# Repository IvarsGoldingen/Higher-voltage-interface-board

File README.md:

# Higher voltage interface board

The device can be used to interface higher voltage DC systems. This specific device is intended for 24VDC.

## Features

* 4 high side transistor outputs;
* 6 inputs using voltage dividers;
* 4 relay outputs;
* 2 buttons;
* 1 LED;
* EEPROM via SPI;
* 2 seperate 5V power inputs: one for relays, the other for other components. Can be jumped together.

## Photos

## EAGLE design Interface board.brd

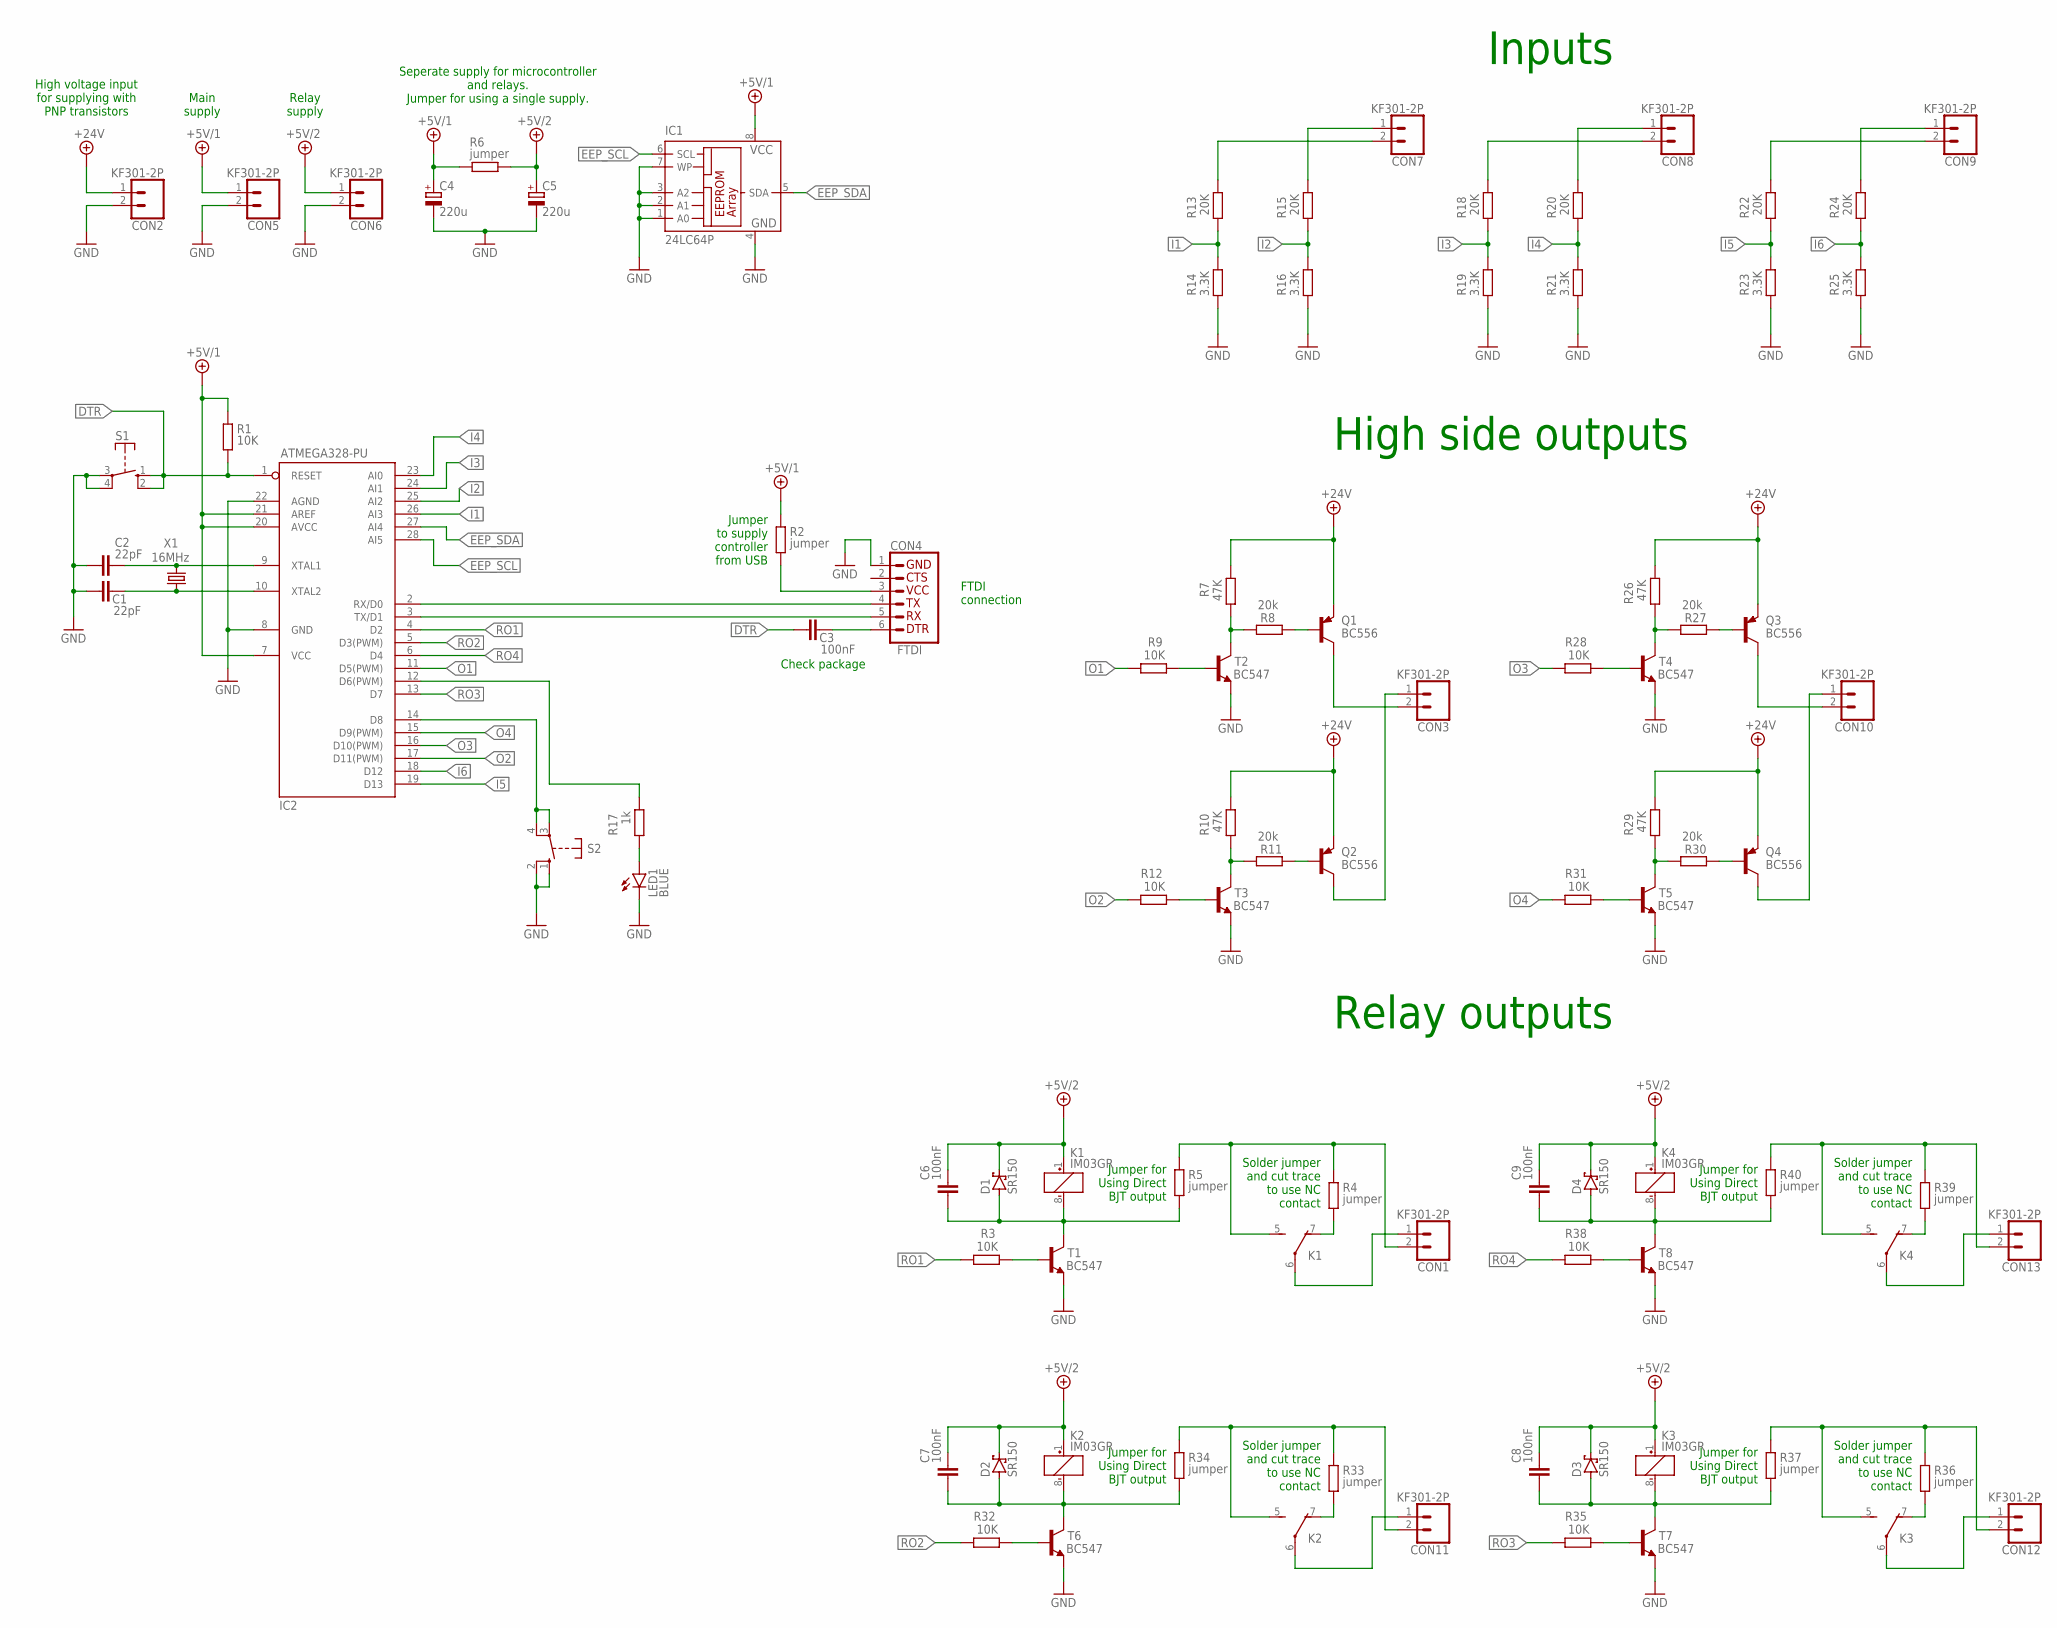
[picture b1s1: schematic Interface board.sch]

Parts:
C1, C2: 22pF; C050-024X044
C3, C6, C7, C8, C9: 100nF; C050-024X044
C4, C5: 220u; E5-10,5
CON1, CON2, CON3, CON5, CON6, CON7, CON8, CON9, CON10, CON11, CON12, CON13: KF301-2P
CON4: FTDI; 1X06_W_REC_GND
D1, D2, D3, D4: SR150; DO41-7.6
IC1: 24LC64P; DIL8
IC2: ATMEGA328-PU; DIL28-3
K1, K2, K3, K4: IM03GR
LED1: BLUE; LED5MM
Q1, Q2, Q3, Q4: BC556; TO92-EBC
R1, R3, R9, R12, R28, R31, R32, R35, R38: 10K; 0204/7
R2, R4, R5, R6, R33, R34, R36, R37, R39, R40: jumper; R0805
R7, R10, R26, R29: 47K; 0204/7
R8, R11, R27, R30: 20k; 0204/7
R13, R15, R18, R20, R22, R24: 20K; 0204/7
R14, R16, R19, R21, R23, R25: 3.3K; 0204/7
R17: 1k; 0204/7
S1, S2: RACON12
T1, T2, T3, T4, T5, T6, T7, T8: BC547; TO92
X1: 16MHz; HC49

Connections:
+5V/1: C4.+, CON5.1, IC1.8 (VCC), IC2.7 (VCC), IC2.20 (AVCC), IC2.21 (AREF), R1.1, R2.1, R6.1
+5V/2: C5.+, C6.1, C7.1, C8.1, C9.1, CON6.1, D1.C, D2.C, D3.C, D4.C, K1.1 (+), K2.1 (+), K3.1 (+), K4.1 (+), R6.2
+24V: CON2.1, Q1.E, Q2.E, Q3.E, Q4.E, R7.2, R10.2, R26.2, R29.2
DTR: C3.2, IC2.1 (RESET), R1.2, S1.1 (S), S1.2 (S)
EEP_SCL: IC1.6 (SCL), IC2.28 (AI5)
EEP_SDA: IC1.5 (SDA), IC2.27 (AI4)
GND: C1.2, C2.2, C4.-, C5.-, CON2.2, CON4.1 (6), CON5.2, CON6.2, IC1.1 (A0), IC1.2 (A1), IC1.3 (A2), IC1.4 (GND), IC1.7 (WP), IC2.8 (GND), IC2.22 (AGND), LED1.K (C), R14.1, R16.1, R19.1, R21.1, R23.1, R25.1, S1.3, S1.4, S2.1 (S), S2.2 (S), T1.1 (E), T2.1 (E), T3.1 (E), T4.1 (E), T5.1 (E), T6.1 (E), T7.1 (E), T8.1 (E)
I1: IC2.26 (AI3), R13.1, R14.2
I2: IC2.25 (AI2), R15.1, R16.2
I3: IC2.24 (AI1), R18.1, R19.2
I4: IC2.23 (AI0), R20.1, R21.2
I5: IC2.19 (D13), R22.1, R23.2
I6: IC2.18 (D12), R24.1, R25.2
unnamed: C1.1, IC2.10 (XTAL2), X1.2
unnamed: C2.1, IC2.9 (XTAL1), X1.1
unnamed: IC2.12 (D6(PWM)), R17.2
unnamed: CON4.4 (3), IC2.2 (RX/D0)
unnamed: CON4.5 (2), IC2.3 (TX/D1)
unnamed: C3.1, CON4.6 (1)
unnamed: IC2.14 (D8), S2.3, S2.4
unnamed: CON4.3 (4), R2.2
unnamed: R3.2, T1.2 (B)
unnamed: R9.2, T2.2 (B)
unnamed: CON1.1, K1.6
unnamed: K1.7 (O), R4.2
unnamed: CON1.2, K1.5 (S), R4.1, R5.1
unnamed: R38.2, T8.2 (B)
unnamed: R7.1, R8.2, T2.3 (C)
unnamed: Q1.B, R8.1
unnamed: C6.2, D1.A, K1.8 (-), R5.2, T1.3 (C)
unnamed: R10.1, R11.2, T3.3 (C)
unnamed: Q2.B, R11.1
unnamed: R12.2, T3.2 (B)
unnamed: CON3.2, Q1.C
unnamed: CON3.1, Q2.C
unnamed: R32.2, T6.2 (B)
unnamed: CON11.1, K2.6
unnamed: CON13.1, K4.6
unnamed: CON7.2, R13.2
unnamed: CON13.2, K4.5 (S), R39.1, R40.1
unnamed: CON7.1, R15.2
unnamed: LED1.A, R17.1
unnamed: CON9.2, R22.2
unnamed: CON8.2, R18.2
unnamed: CON9.1, R24.2
unnamed: CON8.1, R20.2
unnamed: R26.1, R27.2, T4.3 (C)
unnamed: Q3.B, R27.1
unnamed: K4.7 (O), R39.2
unnamed: CON11.2, K2.5 (S), R33.1, R34.1
unnamed: K2.7 (O), R33.2
unnamed: C9.2, D4.A, K4.8 (-), R40.2, T8.3 (C)
unnamed: C7.2, D2.A, K2.8 (-), R34.2, T6.3 (C)
unnamed: R28.2, T4.2 (B)
unnamed: R29.1, R30.2, T5.3 (C)
unnamed: Q4.B, R30.1
unnamed: R31.2, T5.2 (B)
unnamed: CON10.2, Q3.C
unnamed: CON10.1, Q4.C
unnamed: R35.2, T7.2 (B)
unnamed: CON12.1, K3.6
unnamed: CON12.2, K3.5 (S), R36.1, R37.1
unnamed: K3.7 (O), R36.2
unnamed: C8.2, D3.A, K3.8 (-), R37.2, T7.3 (C)
O1: IC2.11 (D5(PWM)), R9.1
O2: IC2.17 (D11(PWM)), R12.1
O3: IC2.16 (D10(PWM)), R28.1
O4: IC2.15 (D9(PWM)), R31.1
RO1: IC2.4 (D2), R3.1
RO2: IC2.5 (D3(PWM)), R32.1
RO3: IC2.13 (D7), R35.1
RO4: IC2.6 (D4), R38.1

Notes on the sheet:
FTDI connection
Check package
Jumper to supply controller from USB
Solder jumper and cut trace to use NC contact
Jumper for Using Direct BJT output
Seperate supply for microcontroller and relays. Jumper for using a single supply.
High voltage input for supplying with PNP transistors
Main supply
Relay supply
Inputs
High side outputs
Relay outputs

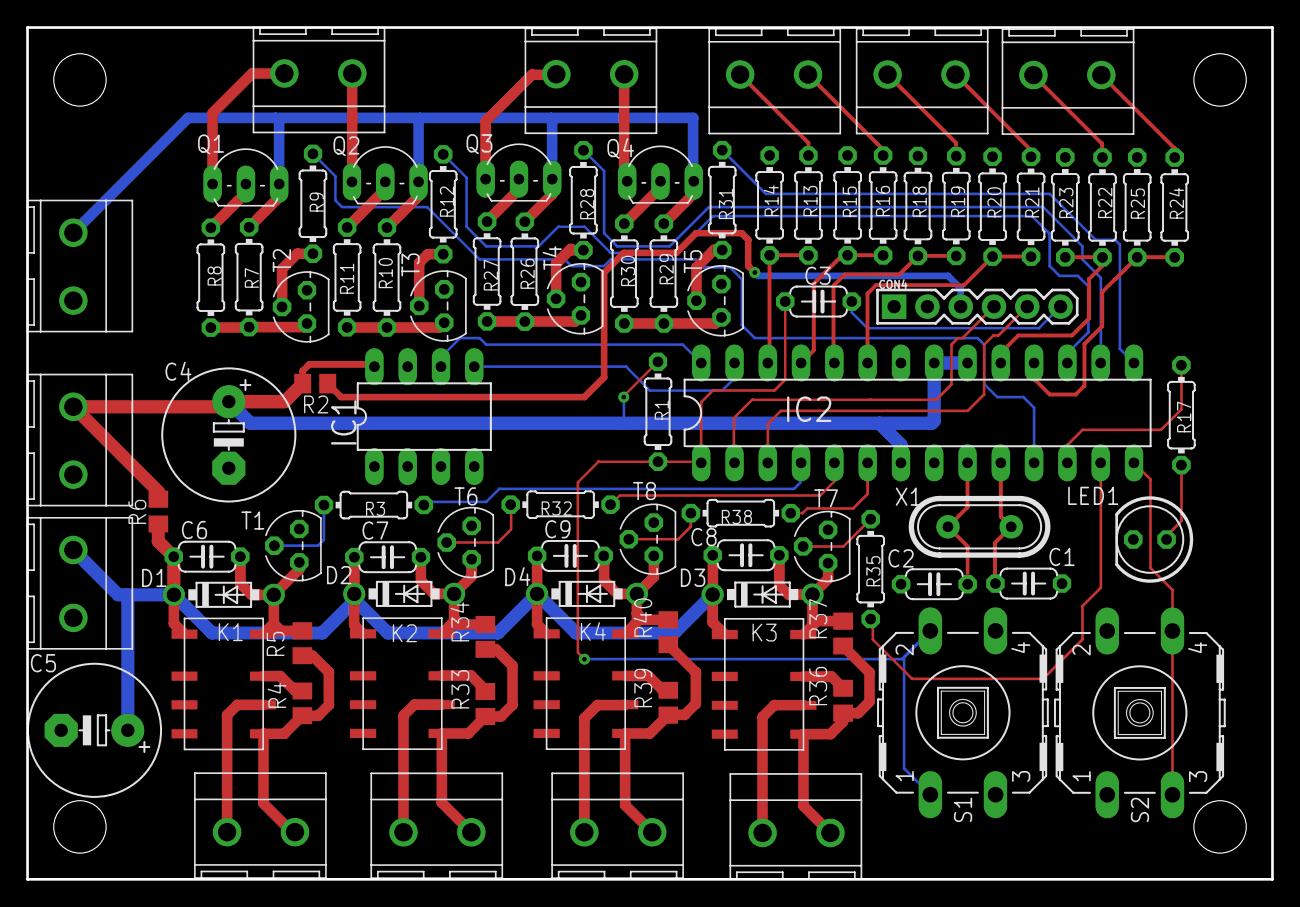
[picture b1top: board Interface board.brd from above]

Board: 2 copper layers, 95.0 x 65.0 mm, 88 parts (0 on the bottom side), 72 nets.

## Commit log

2019-05-08 First version
    First version of interface board
2019-05-13 Updated readme
    Added info and pictures
2019-05-20 Update README.md
    Picture of soldered PCB added
